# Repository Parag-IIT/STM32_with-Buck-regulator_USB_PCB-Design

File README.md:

Sure! Here’s a README.md file for your GitHub repository:

---

# STM32 + USB + Buck Converter PCB Design

Welcome to the STM32 + USB + Buck Converter PCB Design project! This repository contains all the files and documentation for designing a PCB using KiCad that integrates an STM32 microcontroller, a USB interface, and a buck converter.

## Project Overview

This project demonstrates how to create a compact and efficient PCB that combines:
- **STM32 Microcontroller**: Provides robust processing power for a variety of applications.
- **USB Interface**: Enables seamless connectivity for data transfer and device programming.
- **Buck Converter**: Ensures efficient power management and stable performance.

## Applications

This PCB design can be used in various practical applications, including but not limited to:
- USB-Powered Devices
- Data Acquisition Systems
- IoT Gateways
- Smart Home Automation
- Robotics and Automation

## Repository Contents

- `schematics/`: Contains the KiCad schematic files.
- `pcb_layout/`: Contains the KiCad PCB layout files.
- `gerber_files/`: Contains the Gerber files for manufacturing the PCB.
- `bom/`: Bill of Materials listing all components used.
- `docs/`: Additional documentation, including design notes and application examples.
- `images/`: Rendered images of the PCB design.

## Getting Started

### Prerequisites

To work with the files in this repository, you will need:
- [KiCad](https://kicad.org/) (version 6.0 or higher)

### Instructions

1. Open the project in KiCad:
   - Launch KiCad and open the project file located in the `schematics/` directory.
2. Review and modify the schematic:
   - Make any necessary adjustments to the schematic as per your requirements.
3. Generate the netlist:
   - Generate the netlist from the schematic to be used in the PCB layout.
4. Design the PCB layout:
   - Open the PCB layout file in the `pcb_layout/` directory and place the components, route traces, and ensure all design rules are met.
5. Generate Gerber files:
   - Once the PCB layout is complete, generate the Gerber files for manufacturing.

## Usage

### Programming and Debugging

The USB interface allows for easy programming and debugging of the STM32 microcontroller. Connect your development board to a computer via USB and use your preferred IDE (e.g., STM32CubeIDE) to upload and debug your firmware.

### Power Management

The buck converter efficiently steps down the input voltage to a suitable level for the STM32 and other components, ensuring stable and reliable operation.

## Contributing

Contributions are welcome! If you have any ideas, improvements, or bug fixes, please open an issue or submit a pull request.

## Contact

For any questions or further information, feel free to contact me at [parag067@gamil.com].

---

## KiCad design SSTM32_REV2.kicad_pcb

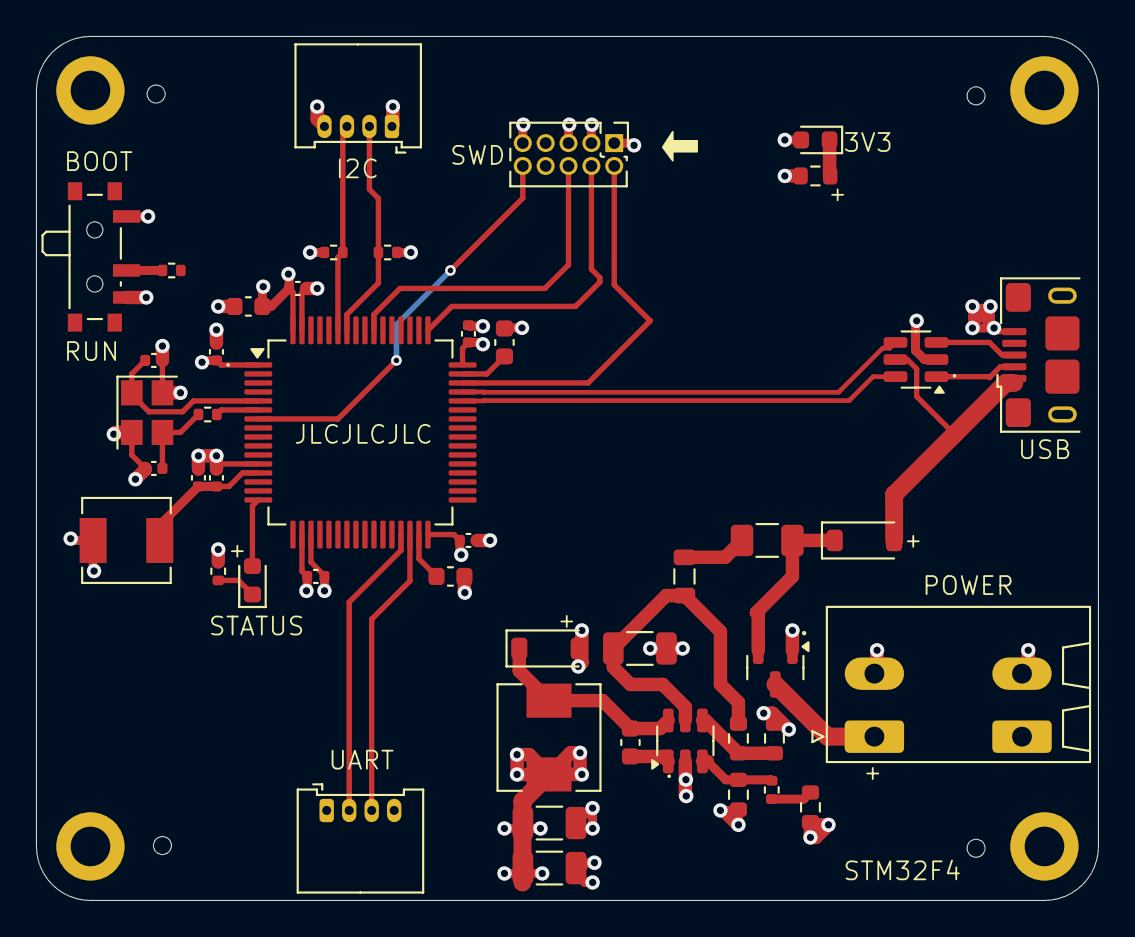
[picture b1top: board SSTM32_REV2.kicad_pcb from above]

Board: 4 copper layers, 59.0 x 48.0 mm, 50 parts (0 on the bottom side), 35 nets.

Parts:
C1, C2: 2u2; C_0603_1608Metric
C3: 4u7; C_0603_1608Metric
C4, C5, C6, C7, C8: 100n; C_0402_1005Metric
C9: 1u; C_0402_1005Metric
C10: 10n; C_0402_1005Metric
C11, C12: 12p; C_0402_1005Metric
C13, C15, C16: 10u; C_1206_3216Metric
C14: 10n; C_0603_1608Metric
D1: BLUE; LED_0603_1608Metric
D2, D3: B5819W; D_SOD-123
D4: RED; LED_0603_1608Metric
F1: 250mA; Fuse_1206_3216Metric
FB1: 600 @ 600MHz; L_0805_2012Metric
H1, H2, H3, H4: MountingHole_Pad; MountingHole_2.2mm_M2_DIN965_Pad
IC1: MP2359DJ-LF-Z; SOT-23-6
J1: Screw_Terminal_01x02; PhoenixContact_SPT_1.5_2-H-3.5_1x02_P3.5mm_Horizontal
J3, J4: Conn_01x04; Molex_PicoBlade_53048-0410_1x04_P1.25mm_Horizontal
J5: USB_B_Micro; USB_Micro-B_Amphenol_10118193-0002LF_Horizontal
J6: Conn_02x05_Odd_Even; PinHeader_2x05_P1.27mm_Vertical
L1: 39n; L_Sunlord_MWSA0402S
L2: 10u; L_Sunlord_MWSA0518S
Q1: AO3401A; SOT-23
R1: 10k; R_0402_1005Metric
R2: 47; R_0402_1005Metric
R3: 1K5; R_0402_1005Metric
R4: 100k; R_0603_1608Metric
R5: 68k; R_0603_1608Metric
R6: 47k; R_0603_1608Metric
R7: 15k; R_0402_1005Metric
R8: 270; R_0603_1608Metric
R9, R10: 2K2; R_0402_1005Metric
R11: 1K; R_0603_1608Metric
SW1: SW_SPDT; SW_SPDT_PCM12
U1: STM32F405RGT6; LQFP-64_10x10mm_P0.5mm
U3: USBLC6-2SC6; SOT-23-6
Y1: 16 MHz; Crystal_SMD_3225-4Pin_3.2x2.5mm

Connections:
+3.3V: C3.1, C4.1, C5.1, C6.1, C7.1, C8.1, C15.1, C16.1, D4.2 (A), J3.1, J4.1, J6.1, L1.1, L2.2, R6.1, R9.1, R10.1, SW1.1 (A), U1.1 (VBAT), U1.19 (VDD), U1.32 (VDD), U1.48 (VDD), U1.64 (VDD)
+3.3VA: C9.1, C10.1, L1.2, U1.13 (VDDA)
+5V: D3.2 (A), J5.1 (VBUS), U3.5 (VBUS)
+12V: J1.1, Q1.3 (D)
BOOT0: R1.2, U1.60 (BOOT0)
BUCK_BST: C14.1, IC1.1 (BST)
BUCK_EN: IC1.4 (EN), R4.2, R5.1
BUCK_FB: IC1.3 (FB), R6.2, R7.1
BUCK_IN: C13.1, FB1.2, IC1.5 (IN), R4.1
BUCK_SW: C14.2, D2.1 (K), IC1.6 (SW), L2.1
GND: C1.2, C2.2, C3.2, C4.2, C5.2, C6.2, C7.2, C8.2, C9.2, C10.2, C11.2, C12.2, C13.2, C15.2, C16.2, D2.2 (A), H1.1, H2.1, H3.1, H4.1, IC1.2 (GND), J1.2, J3.4, J4.4, J5.5 (GND), J6.3, J6.5, J6.9, Q1.1 (G), R3.2, R5.2, R8.2, R11.2, SW1.3 (C), U1.12 (VSSA), U1.18 (VSS), U1.63 (VSS), U3.2 (GND), Y1.2, Y1.4
HSE_IN: C12.1, U1.5 (PH0), Y1.1
HSE_OUT: R2.1, U1.6 (PH1)
I2C1_SCL: J3.2, R9.2, U1.58 (PB6)
I2C1_SDA: J3.3, R10.2, U1.59 (PB7)
LED_STATUS: D1.2 (A), U1.16 (PA2)
NRST: J6.10, U1.7 (NRST)
unnamed: C11.1, R2.2, Y1.3
unnamed: D1.1 (K), R3.1
unnamed: D3.1 (K), F1.2, Q1.2 (S)
unnamed: D4.1 (K), R11.1
unnamed: F1.1, FB1.1
unnamed: R7.2, R8.1
unnamed: R1.1, SW1.2 (B)
unnamed: C2.1, U1.31 (VCAP_1)
unnamed: C1.1, U1.47 (VCAP_2)
SWCLK: J6.4, U1.49 (PA14)
SWDIO: J6.2, U1.46 (PA13)
SWO: J6.6, U1.55 (PB3)
UART3_RX: J4.3, U1.30 (PB11)
UART3_TX: J4.2, U1.29 (PB10)
USB_CONN_D+: J5.3 (D+), U3.3 (I/O2)
USB_CONN_D-: J5.2 (D-), U3.1 (I/O1)
USB_D+: U1.45 (PA12), U3.4 (I/O2)
USB_D-: U1.44 (PA11), U3.6 (I/O1)
